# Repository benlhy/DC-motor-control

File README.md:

This a DC motor controller built around the TI TIVA TM4C123 chip. It has position and velocity control and can be linked up to form a multi-axis system. 

# Layouts

Layout for the standalone board is here:

Boost board layout:

# Programming

To program this board you will need Launchpad that has the programming pins broken out. Please see the [programming repo](https://github.com/benlhy/DC-Control-Module) for more details.

# Design Decisions

## Motor Driver
TB6612FNG - 2.5 ~ 13.5V, 1.3A per channel, max 3.2A
DRV8848 - 4 ~ 18V, 1A per channel, max 2A

## Regulator
MIC5219 - 20V input range, and comes in 5V flavour and 3.3V flavour

## Crystal
NDK (NX3325SA) was chosen because guidelines indicated that Max DI(uW) > 200, and most of Abracon's crystals had a max DI of 100. Anything with CL greater than 18uF was also not acceptable. From Table 30-24, the recommended component values were 12pF for the capacitors and Rs of 2k. This was the smallest crystal that was recommended. Note that it is NX3225GA that was recommended, but the difference appears to be ordering information.

## Reset
A 100R resistor is placed in series with the reset switch to prevent ringing as suggested in the design guide.

# References
1. http://www.ti.com/lit/ds/symlink/tm4c123gh6pm.pdf
2. http://www.ti.com/lit/an/spma059/spma059.pdf

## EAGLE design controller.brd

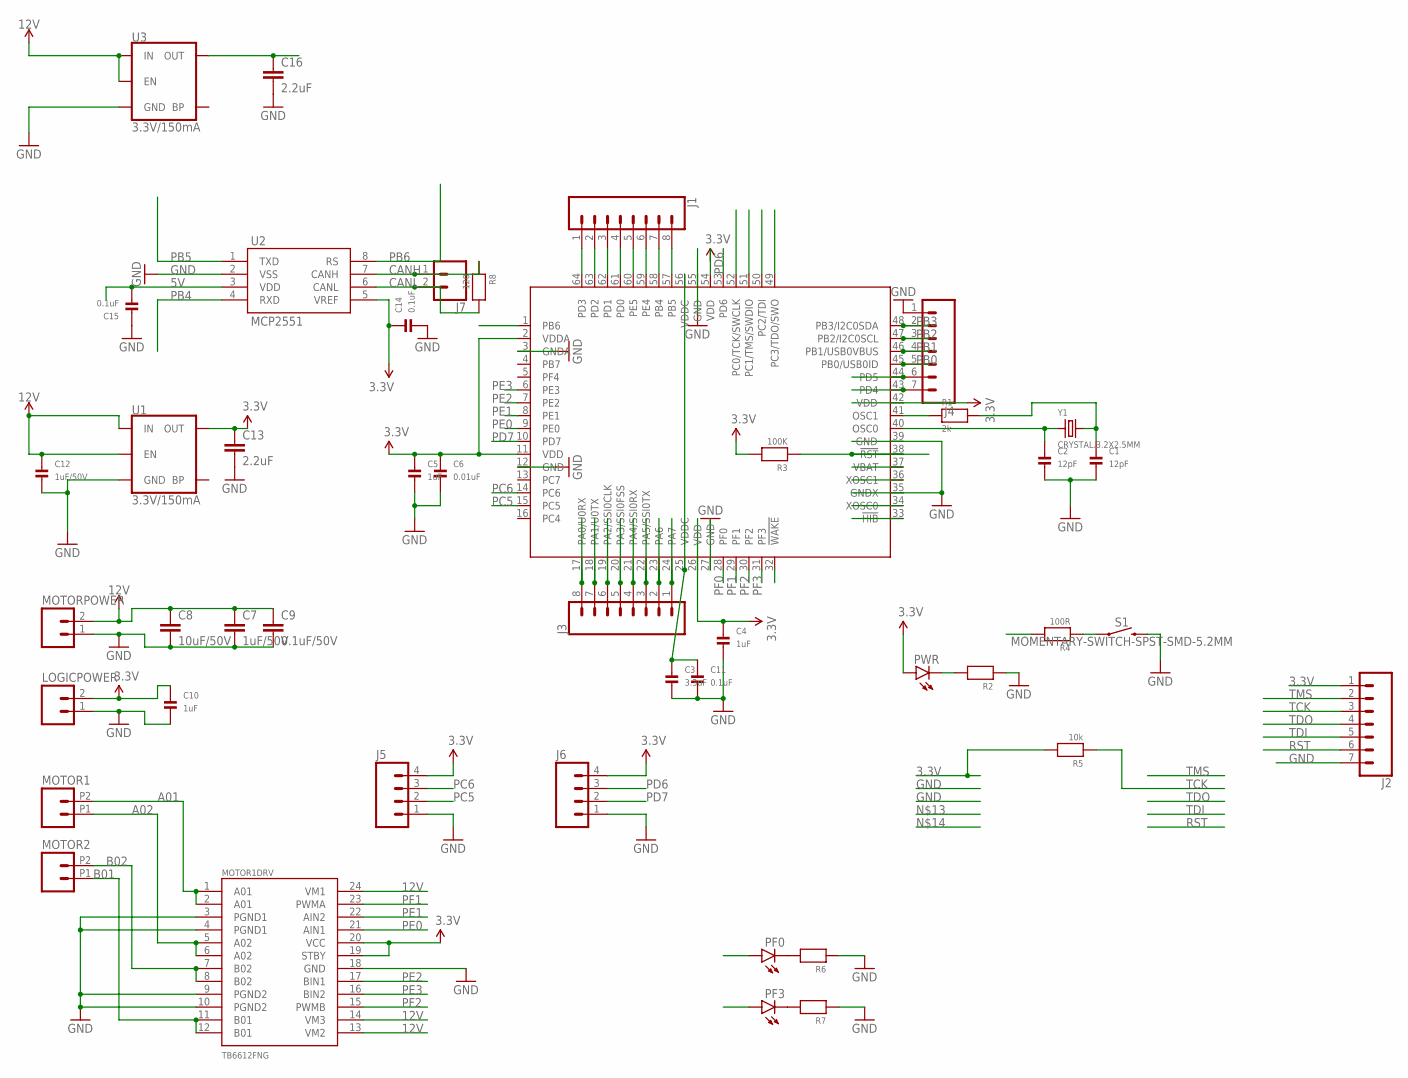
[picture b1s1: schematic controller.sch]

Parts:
C1, C2: 12pF; _0603MP
C3: 3.3uF; _0603MP
C4, C5, C10: 1uF; _0603MP
C6: 0.01uF; _0603MP
C7: 1uF/50V; 0603-CAP
C8: 10uF/50V; 0805-CAP
C9: 0.1uF/50V; 0603-CAP
C11, C14, C15: 0.1uF; _0603MP
C12: 1uF/50V; _0603MP
C13, C16: 2.2uF; 0805
IC1: TM4C123[7,G]XXPM; PM_S-PQFP-G64
J1, J3: CONN_08"; 1X08@1
J2: CONN_07; 1X07@1
J4: M07; 1X07
J5, J6: M04PTH; 1X04
J7: CONN_02; 1X02
LOGICPOWER: M02PTH; 1X02@1
MOTOR1, MOTOR2: M022.54MM_SCREWTERM; 1X02_2.54_SCREWTERM@1
MOTOR1DRV: TB6612FNG; SSOP24
MOTORPOWER: M02PTH; 1X02@1
PF0, PF3: LED0603; LED-0603
PWR: LED0603; LED-0603
R1: 2k; _0603MP
R2, R6, R7: RESISTOR_0603MP; _0603MP
R3: 100K; _0603MP
R4: 100R; _0603MP
R5: 10k; _0603MP
R8: 120; _0603MP
S1: MOMENTARY-SWITCH-SPST-SMD-5.2MM; TACTILE_SWITCH_SMD_5.2MM
U1, U3: 3.3V/150mA; SOT23-5
U2: MCP2551; SO08
Y1: CRYSTAL.3.2X2.5MM; 3.2X2.5MM

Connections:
3.3V: C4.1, C5.1, C6.1, C10.1, C13.1, C14.1, IC1.2 (VDDA), IC1.11 (VDD), IC1.26 (VDD), IC1.42 (VDD), IC1.54 (VDD), J2.1, J5.4, J6.4, LOGICPOWER.2, MOTOR1DRV.19 (STBY), MOTOR1DRV.20 (VCC), PWR.A, R3.2, R5.2, U1.5 (OUT), U2.5 (VREF)
5V: C15.2, C16.1, U2.3 (VDD), U3.5 (OUT)
12V: C7.1, C8.1, C9.1, C12.1, MOTOR1DRV.13 (VM2), MOTOR1DRV.14 (VM3), MOTOR1DRV.24 (VM1), MOTORPOWER.2, U1.1 (IN), U1.3 (EN), U3.1 (IN), U3.3 (EN)
A01: MOTOR1.P2 (2), MOTOR1DRV.1 (A01), MOTOR1DRV.2 (A01)
A02: MOTOR1.P1 (1), MOTOR1DRV.5 (A02), MOTOR1DRV.6 (A02)
B01: MOTOR1DRV.11 (B01), MOTOR1DRV.12 (B01), MOTOR2.P1 (1)
B02: MOTOR1DRV.7 (B02), MOTOR1DRV.8 (B02), MOTOR2.P2 (2)
CANH: J7.1, R8.1, U2.7 (CANH)
CANL: J7.2, R8.2, U2.6 (CANL)
GND: C1.2, C2.2, C3.2, C4.2, C5.2, C6.2, C7.2, C8.2, C9.2, C10.2, C11.2, C12.2, C13.2, C14.2, C15.1, C16.2, IC1.3 (GNDA), IC1.12 (GND), IC1.27 (GND), IC1.35 (GNDX), IC1.39 (GND), IC1.55 (GND), J2.7, J4.1, J5.1, J6.1, LOGICPOWER.1, MOTOR1DRV.3 (PGND1), MOTOR1DRV.4 (PGND1), MOTOR1DRV.9 (PGND2), MOTOR1DRV.10 (PGND2), MOTOR1DRV.18 (GND), MOTORPOWER.1, R2.1, R6.1, R7.1, S1.3 (2), U1.2 (GND), U2.2 (VSS), U3.2 (GND)
unnamed: IC1.41 (OSC1), R1.1
unnamed: C2.1, IC1.40 (OSC0), Y1.1
unnamed: C3.1, C11.1, IC1.25 (VDDC), IC1.56 (VDDC)
unnamed: C1.1, R1.2, Y1.3 (2)
unnamed: PF0.C, R6.2
unnamed: PF3.C, R7.2
unnamed: IC1.64 (PD3), J1.1
unnamed: IC1.63 (PD2), J1.2
unnamed: IC1.62 (PD1), J1.3
unnamed: IC1.61 (PD0), J1.4
unnamed: IC1.60 (PE5), J1.5
unnamed: IC1.59 (PE4), J1.6
unnamed: IC1.24 (PA7), J3.1
unnamed: IC1.23 (PA6), J3.2
unnamed: IC1.22 (PA5/SSI0TX), J3.3
unnamed: IC1.21 (PA4/SSI0RX), J3.4
unnamed: IC1.20 (PA3/SSI0FSS), J3.5
unnamed: IC1.19 (PA2/SSI0CLK), J3.6
unnamed: IC1.18 (PA1/U0TX), J3.7
unnamed: IC1.17 (PA0/U0RX), J3.8
unnamed: IC1.44 (PD5), J4.6
unnamed: IC1.43 (PD4), J4.7
unnamed: PWR.C, R2.2
unnamed: R4.1, S1.1
PB0: IC1.45 (PB0/USB0ID), J4.5
PB1: IC1.46 (PB1/USB0VBUS), J4.4
PB2: IC1.47 (PB2/I2C0SCL), J4.3
PB3: IC1.48 (PB3/I2C0SDA), J4.2
PB4: IC1.58 (PB4), J1.7, U2.4 (RXD)
PB5: IC1.57 (PB5), J1.8, U2.1 (TXD)
PB6: IC1.1 (PB6), U2.8 (RS)
PC5: IC1.15 (PC5), J5.2
PC6: IC1.14 (PC6), J5.3
PD6: IC1.53 (PD6), J6.3
PD7: IC1.10 (PD7), J6.2
PE0: IC1.9 (PE0), MOTOR1DRV.21 (AIN1)
PE1: IC1.8 (PE1), MOTOR1DRV.22 (AIN2)
PE2: IC1.7 (PE2), MOTOR1DRV.17 (BIN1)
PE3: IC1.6 (PE3), MOTOR1DRV.16 (BIN2)
PF0: IC1.28 (PF0), PF0.A
PF1: IC1.29 (PF1), MOTOR1DRV.23 (PWMA)
PF2: IC1.30 (PF2), MOTOR1DRV.15 (PWMB)
PF3: IC1.31 (PF3), PF3.A
RST: IC1.38 (!RST), J2.6, R3.1, R4.2
TCK: IC1.52 (PC0/TCK/SWCLK), J2.3, R5.1
TDI: IC1.50 (PC2/TDI), J2.5
TDO: IC1.49 (PC3/TDO/SWO), J2.4
TMS: IC1.51 (PC1/TMS/SWDIO), J2.2

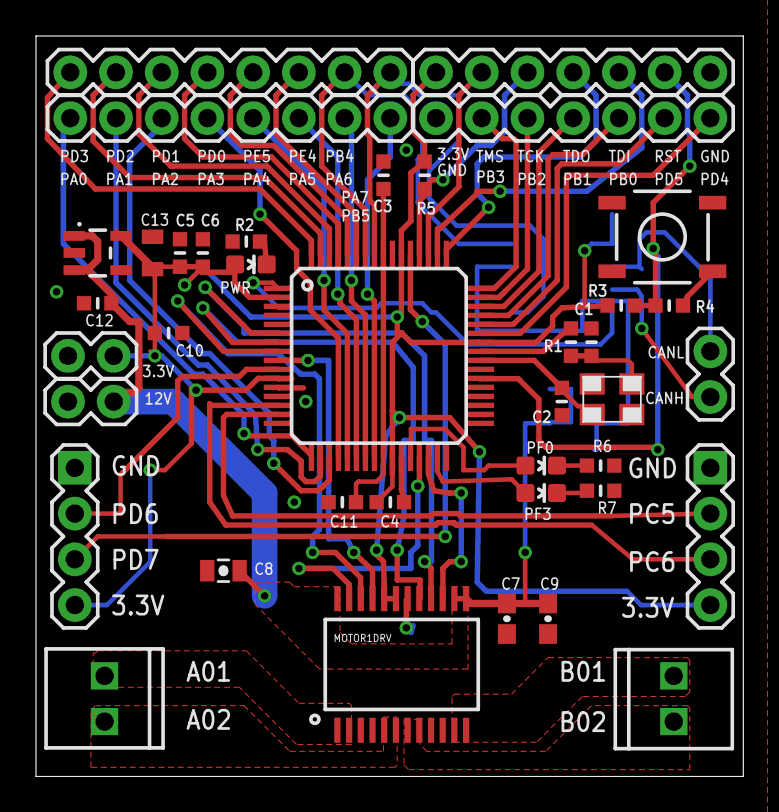
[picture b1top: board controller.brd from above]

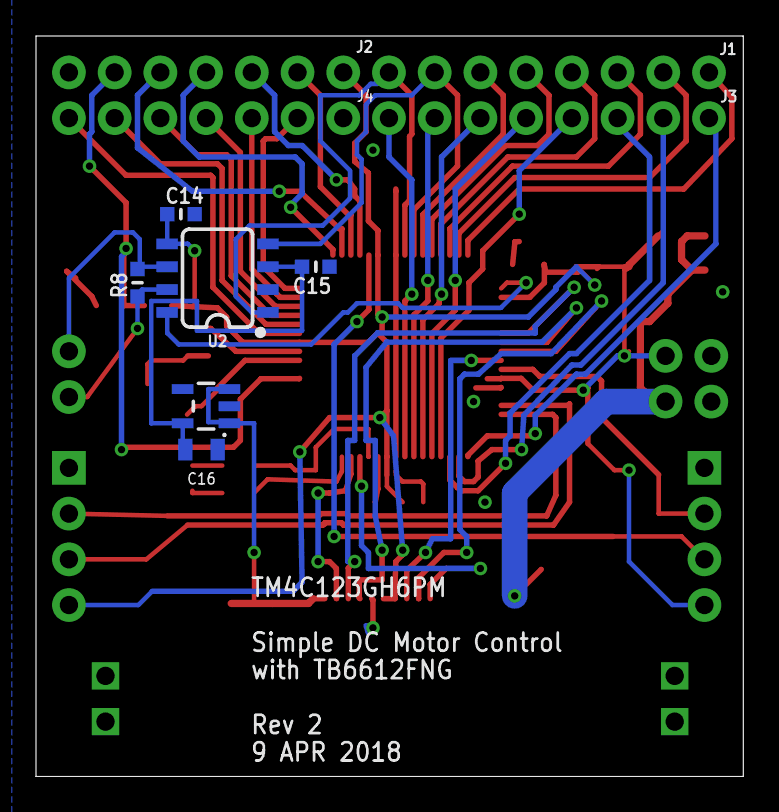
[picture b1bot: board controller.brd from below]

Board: 2 copper layers, 39.3 x 41.1 mm, 45 parts (6 on the bottom side), 58 nets.

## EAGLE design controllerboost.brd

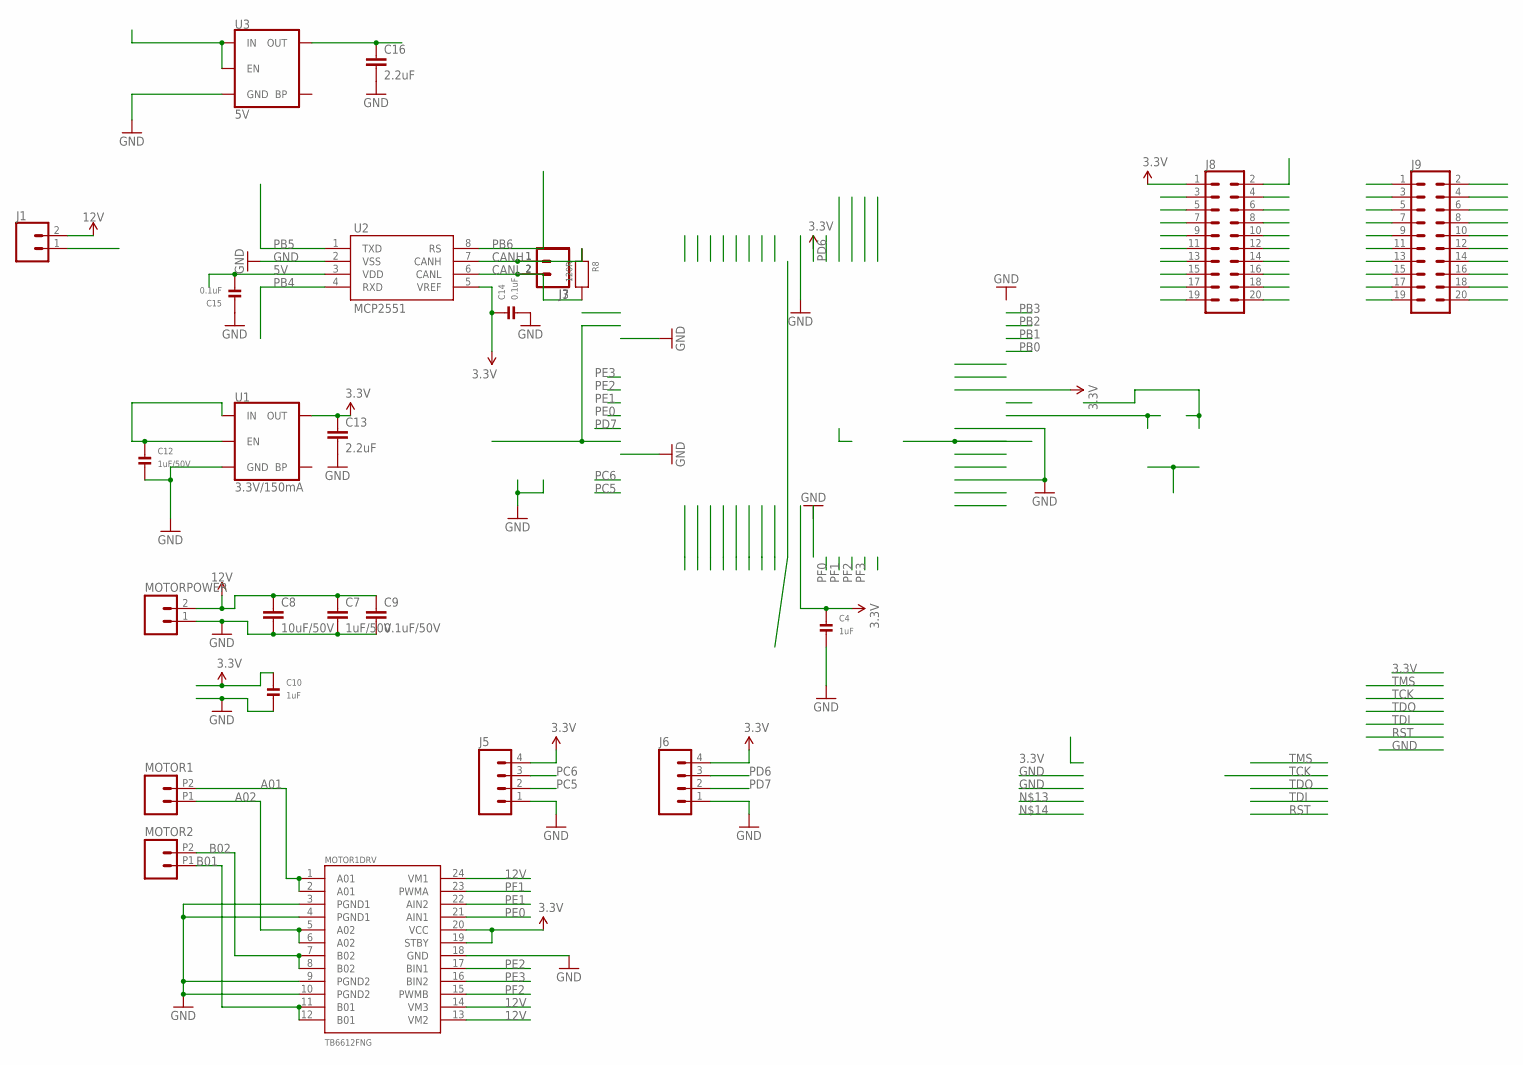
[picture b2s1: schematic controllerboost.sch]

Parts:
C4, C10: 1uF; _0603MP
C7: 1uF/50V; 0603-CAP
C8: 10uF/50V; 0805-CAP
C9: 0.1uF/50V; 0603-CAP
C12: 1uF/50V; _0603MP
C13, C16: 2.2uF; 0805
C14, C15: 0.1uF; _0603MP
J1, J3, J7: CONN_02; 1X02
J5, J6: M04PTH; 1X04
J8, J9: CONN_10X2; 2X10
MOTOR1, MOTOR2: M022.54MM_SCREWTERM; 1X02_2.54_SCREWTERM@1
MOTOR1DRV: TB6612FNG; SSOP24
MOTORPOWER: M02PTH; 1X02@1
R8: 120R; _0603MP
U1: 3.3V/150mA; SOT23-5
U2: MCP2551; SO08
U3: 5V; SOT23-5

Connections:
3.3V: C4.1, C10.1, C13.1, C14.1, J5.4, J6.4, J8.1, MOTOR1DRV.19 (STBY), MOTOR1DRV.20 (VCC), U1.5 (OUT), U2.5 (VREF)
5V: C15.2, C16.1, J8.2, U2.3 (VDD), U3.5 (OUT)
12V: C7.1, C8.1, C9.1, J1.2, MOTOR1DRV.13 (VM2), MOTOR1DRV.14 (VM3), MOTOR1DRV.24 (VM1), MOTORPOWER.2
A01: MOTOR1.P2 (2), MOTOR1DRV.1 (A01), MOTOR1DRV.2 (A01)
A02: MOTOR1.P1 (1), MOTOR1DRV.5 (A02), MOTOR1DRV.6 (A02)
B01: MOTOR1DRV.11 (B01), MOTOR1DRV.12 (B01), MOTOR2.P1 (1)
B02: MOTOR1DRV.7 (B02), MOTOR1DRV.8 (B02), MOTOR2.P2 (2)
CANH: J3.1, J7.1, R8.1, U2.7 (CANH)
CANL: J3.2, J7.2, R8.2, U2.6 (CANL)
GND: C4.2, C7.2, C8.2, C9.2, C10.2, C12.2, C13.2, C14.2, C15.1, C16.2, J5.1, J6.1, J8.4, J9.2, MOTOR1DRV.3 (PGND1), MOTOR1DRV.4 (PGND1), MOTOR1DRV.9 (PGND2), MOTOR1DRV.10 (PGND2), MOTOR1DRV.18 (GND), MOTORPOWER.1, U1.2 (GND), U2.2 (VSS), U3.2 (GND)
P2L: C12.1, J1.1, U1.1 (IN), U1.3 (EN), U3.1 (IN), U3.3 (EN)
PA2: J9.20
PA3: J9.18
PA4: J9.16
PA5: J8.15
PA6: J8.17
PA7: J8.19
PB0: J8.5
PB1: J8.7
PB2: J9.4
PB3: J9.5
PB4: J8.13, U2.4 (RXD)
PB5: J8.3, U2.1 (TXD)
PB6: J9.14, U2.8 (RS)
PB7: J9.12
PC4: J9.7
PC5: J5.2, J9.9
PC6: J5.3, J9.11
PC7: J9.13
PD0: J8.6
PD1: J8.8
PD2: J8.10
PD3: J8.12
PD6: J6.3, J9.15
PD7: J6.2, J9.17
PE0: J9.6, MOTOR1DRV.21 (AIN1)
PE1: J8.14, MOTOR1DRV.22 (AIN2)
PE2: J8.16, MOTOR1DRV.17 (BIN1)
PE3: J8.18, MOTOR1DRV.16 (BIN2)
PE4: J8.9
PE5: J8.11
PF0: J9.8
PF1: J8.20, MOTOR1DRV.23 (PWMA)
PF2: J9.1, MOTOR1DRV.15 (PWMB)
PF3: J9.3
PF4: J9.19
RST: J9.10

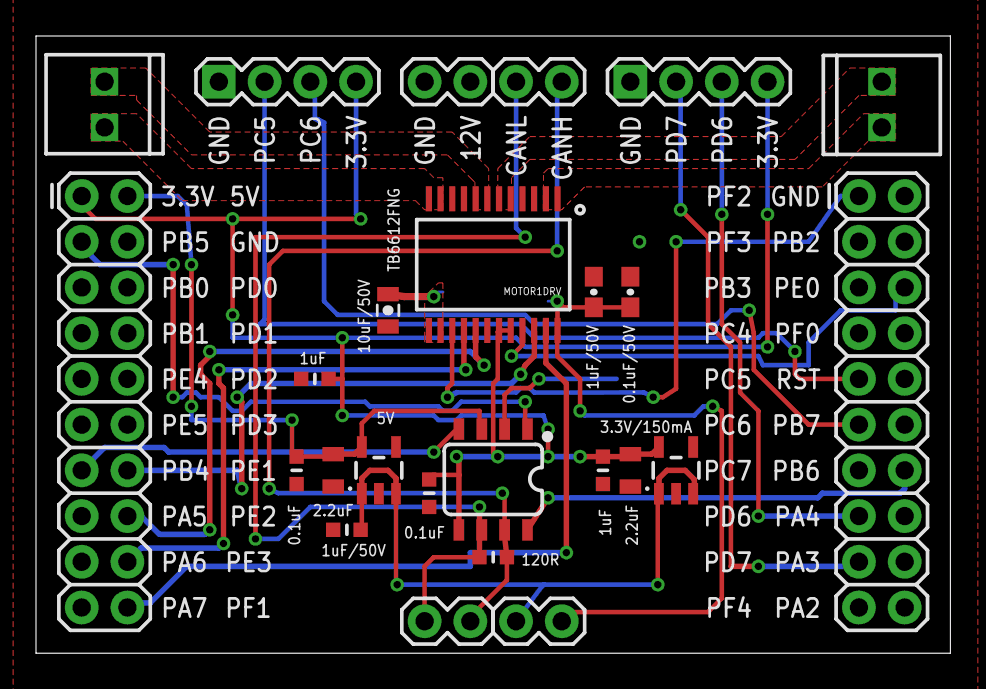
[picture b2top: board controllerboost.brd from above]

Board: 2 copper layers, 50.8 x 34.3 mm, 25 parts (0 on the bottom side), 24 nets.

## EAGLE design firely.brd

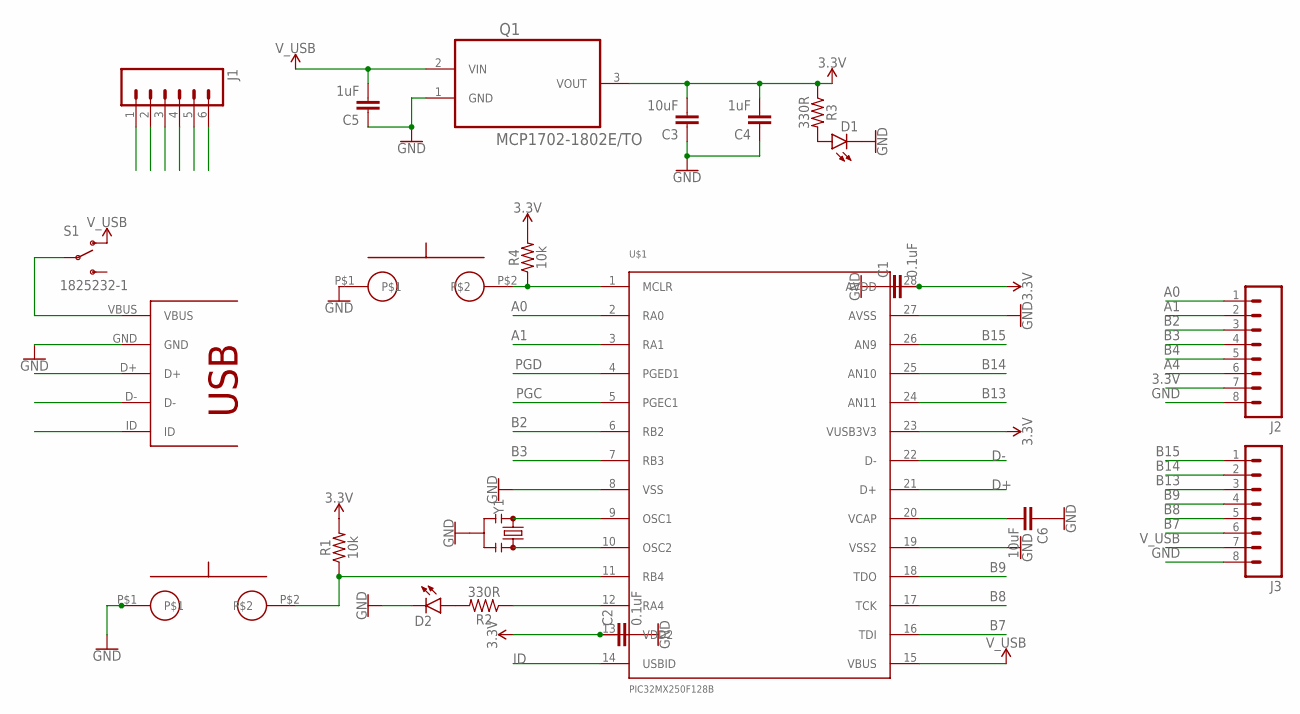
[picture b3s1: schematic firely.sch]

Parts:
C1, C2: 0.1uF; PTH_VERT_CAP
C3, C6: 10uF; PTH_VERT_CAP
C4, C5: 1uF; PTH_VERT_CAP
D1, D2: LED3MM
J1: M06SILK_FEMALE_PTH; 1X06
J2, J3: M08; 1X08_ROUND
Q1: MCP1702-1802E/TO; TO127P254X533-3
R1, R4: 10k; AXIAL-0.3
R2, R3: 330R; AXIAL-0.3
S1: 1825232-1
U$1: PIC32MX250F128B; DIP28
U$2, U$4: EVQ11
U$3: USB_FULL; USB-MB-H
Y1: RESONATORPTH-7.6X3.8; RESONATOR-PTH-7.6X3.8

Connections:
3.3V: C1.P$2 (2), C2.P$1 (1), C3.P$2 (2), C4.P$2 (2), J1.2, J2.7, Q1.3 (VOUT), R1.P$2 (2), R3.P$1 (1), R4.P$2 (2), U$1.13 (VDD2), U$1.23 (VUSB3V3), U$1.28 (AVDD)
A0: J2.1, U$1.2 (RA0)
A1: J2.2, U$1.3 (RA1)
A4: J2.6, R2.P$1 (1), U$1.12 (RA4)
B2: J2.3, U$1.6 (RB2)
B3: J2.4, U$1.7 (RB3)
B4: J2.5, R1.P$1 (1), U$1.11 (RB4), U$2.P$2
B7: J3.6, U$1.16 (TDI)
B8: J3.5, U$1.17 (TCK)
B9: J3.4, U$1.18 (TDO)
B13: J3.3, U$1.24 (AN11)
B14: J3.2, U$1.25 (AN10)
B15: J3.1, U$1.26 (AN9)
D+: U$1.21 (D+), U$3.D+
D-: U$1.22 (D-), U$3.D-
GND: C1.P$1 (1), C2.P$2 (2), C3.P$1 (1), C4.P$1 (1), C5.P$1 (1), C6.P$1 (1), D1.K (C), D2.K (C), J1.3, J2.8, J3.8, Q1.1 (GND), U$1.8 (VSS), U$1.19 (VSS2), U$1.27 (AVSS), U$2.P$1, U$3.GND, U$4.P$1, Y1.2
ID: U$1.14 (USBID), U$3.ID
MCLR: J1.1, R4.P$1 (1), U$1.1 (MCLR), U$4.P$2
unnamed: D2.A, R2.P$2 (2)
unnamed: S1.2, U$3.VBUS
unnamed: D1.A, R3.P$2 (2)
unnamed: U$1.9 (OSC1), Y1.1
unnamed: U$1.10 (OSC2), Y1.3
unnamed: C6.P$2 (2), U$1.20 (VCAP)
PGC: J1.5, U$1.5 (PGEC1)
PGD: J1.4, U$1.4 (PGED1)
V_USB: C5.P$2 (2), J3.7, Q1.2 (VIN), S1.3, U$1.15 (VBUS)

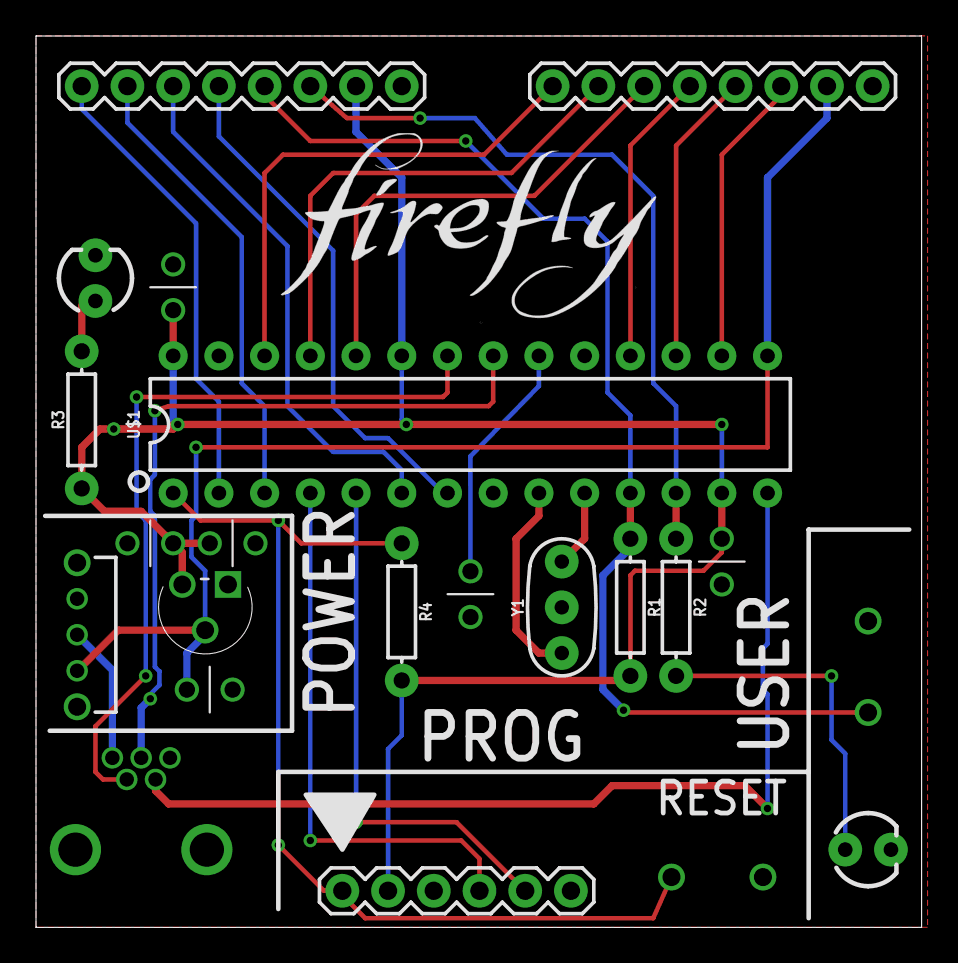
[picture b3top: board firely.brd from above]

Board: 2 copper layers, 49.2 x 49.5 mm, 22 parts (0 on the bottom side), 27 nets.

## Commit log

2018-04-08 Updated board, added onboard 3.3V power, changed crystal size
2018-04-09 Added reference file, updated readME
2018-04-11 Updated with additional PDFs
2018-04-11 Wired it up
2018-04-21 added layout images
2018-04-21 cleaned and updated files
2018-04-21 added image
2018-04-21 Added boost layout
2018-04-21 readme updated
2018-04-23 Update with pictures!
2018-04-23 nothing

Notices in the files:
parts and their libraries:
microbuilder: This work is placed in the public domain, and may be freely used for commercial and non-commercial work with the following conditions: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
SparkFun-Connectors: Licensing: Creative Commons ShareAlike 4.0 International - https://creativecommons.org/licenses/by-sa/4.0
